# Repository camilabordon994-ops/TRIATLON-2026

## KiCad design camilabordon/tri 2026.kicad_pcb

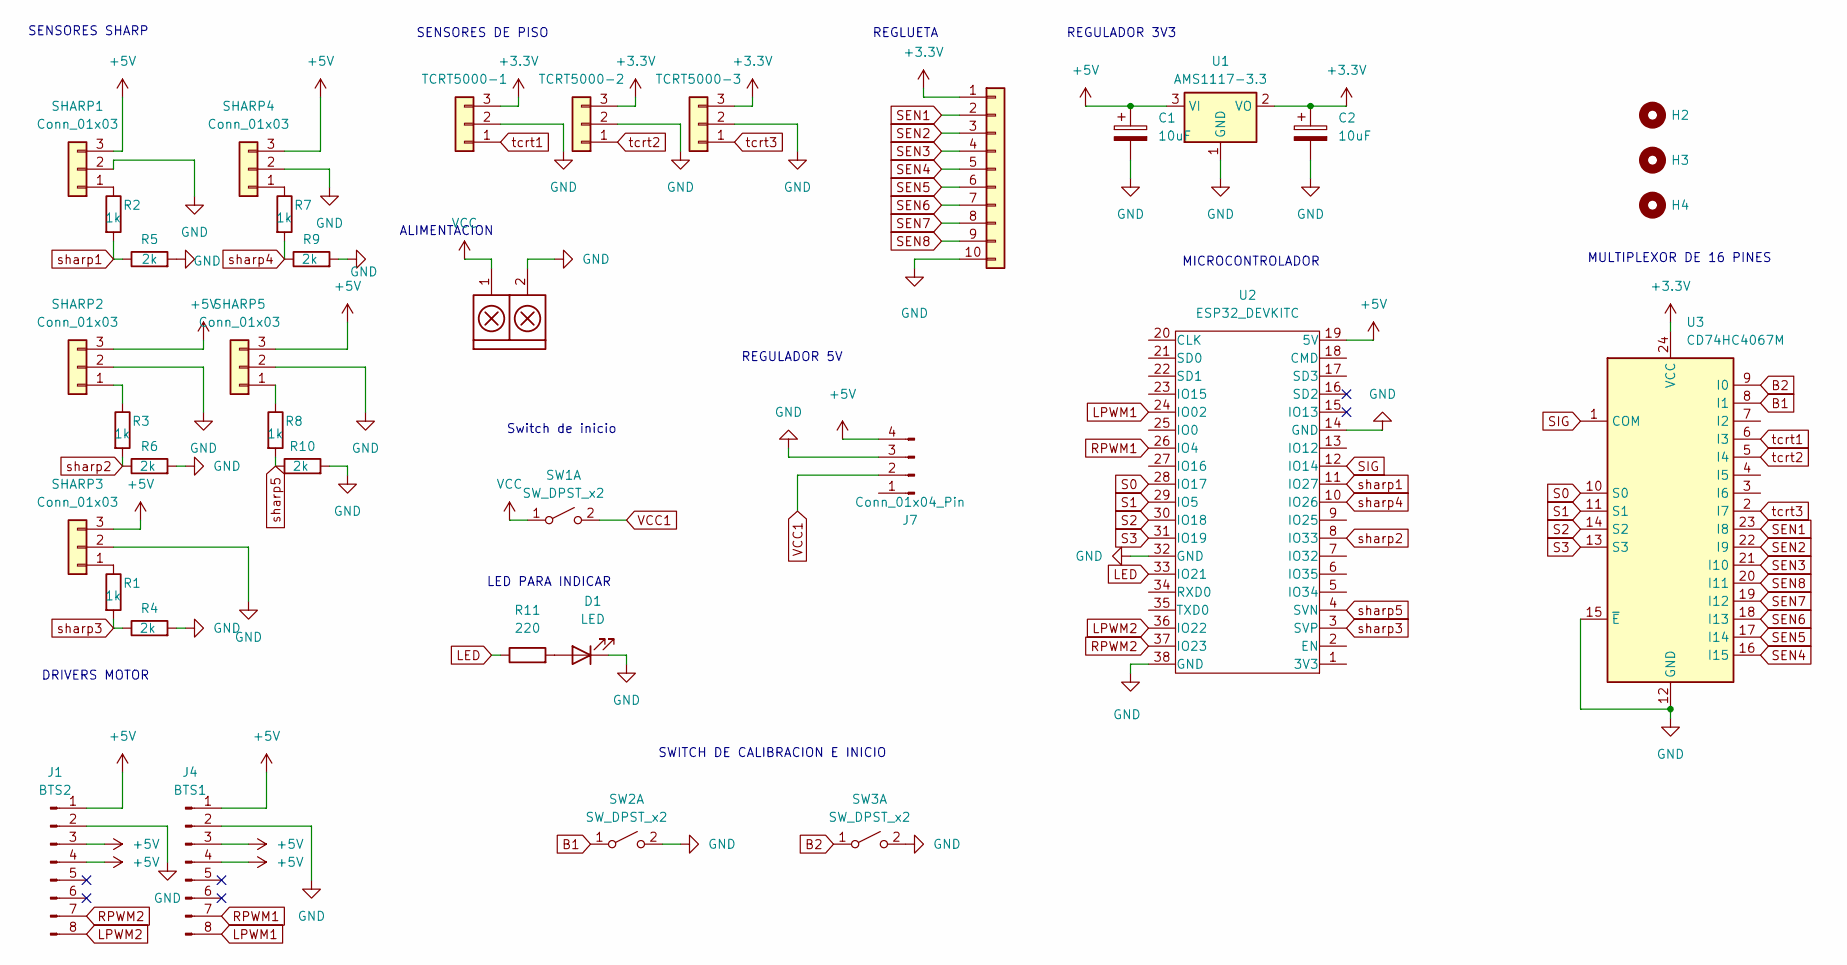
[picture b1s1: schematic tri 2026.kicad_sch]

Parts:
C1, C2: 10uF; C_0805_2012Metric
D1: LED; LED_D5.0mm
H2, H3, H4: Mounting_Hole; MountingHole_3.2mm_M3
J1: BTS2; IDC-Header_2x04_P2.54mm_Vertical
J2: TCRT5000-1; PinHeader_1x03_P2.54mm_Vertical
J3: TB_1X2; AMASS_XT30UPB-F_1x02_P5.0mm_Vertical
J4: BTS1; IDC-Header_2x04_P2.54mm_Vertical
J5: TCRT5000-2; PinHeader_1x03_P2.54mm_Vertical
J6: TCRT5000-3; PinHeader_1x03_P2.54mm_Vertical
J7: Conn_01x04_Pin; Step_Down_Mini
J8: Conn_01x10; JST_XH_S10B-XH-A_1x10_P2.50mm_Horizontal
R1, R2, R3, R7, R8: 1k; R_1206_3216Metric
R4, R5, R6, R9, R10: 2k; R_1206_3216Metric
R11: 220; R_1206_3216Metric
SHARP1, SHARP2, SHARP3, SHARP4, SHARP5: Conn_01x03; JST_XH_S3B-XH-A_1x03_P2.50mm_Horizontal
SW1: SW_DPST_x2; SW_SPDT_TH_Vertical
SW2, SW3: SW_DPST_x2; SW_PUSH_6mm_H5mm
U1: AMS1117-3.3; SOT-223-3_TabPin2
U2: ESP32_DEVKITC; esp32 38 pin usb-c
U3: CD74HC4067M; CD74HC4067_module

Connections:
+3.3V: C2.1, J2.3, J5.3, J6.3, J8.1, U1.2 (VO), U3.24 (VCC)
+5V: C1.1, J1.1, J1.3, J1.4, J4.1, J4.3, J4.4, J7.4, SHARP1.3, SHARP2.3, SHARP3.3, SHARP4.3, SHARP5.3, U1.3 (VI), U2.19 (5V)
B1: SW2.1 (A), U3.8 (I1)
B2: SW3.1 (A), U3.9 (I0)
GND: C1.2, C2.2, D1.1 (K), J1.2, J2.2, J3.2, J4.2, J5.2, J6.2, J7.3, J8.10, R4.2, R5.2, R6.2, R9.2, R10.2, SHARP1.2, SHARP2.2, SHARP3.2, SHARP4.2, SHARP5.2, SW2.2 (B), SW3.2 (B), U1.1 (GND), U2.14 (GND), U2.32 (GND), U2.38 (GND), U3.12 (GND), U3.15 (~E)
LED: R11.1, U2.33 (IO21)
LPWM1: J4.8, U2.24 (IO02)
LPWM2: J1.8, U2.36 (IO22)
unnamed: D1.2 (A), R11.2
unnamed: R2.1, SHARP1.1
unnamed: R3.1, SHARP2.1
unnamed: R1.1, SHARP3.1
unnamed: R7.1, SHARP4.1
unnamed: R8.1, SHARP5.1
RPWM1: J4.7, U2.26 (IO4)
RPWM2: J1.7, U2.37 (IO23)
S0: U2.28 (IO17), U3.10 (S0)
S1: U2.29 (IO5), U3.11 (S1)
S2: U2.30 (IO18), U3.14 (S2)
S3: U2.31 (IO19), U3.13 (S3)
SEN1: J8.2, U3.23 (I8)
SEN2: J8.3, U3.22 (I9)
SEN3: J8.4, U3.21 (I10)
SEN4: J8.5, U3.16 (I15)
SEN5: J8.6, U3.17 (I14)
SEN6: J8.7, U3.18 (I13)
SEN7: J8.8, U3.19 (I12)
SEN8: J8.9, U3.20 (I11)
SIG: U2.12 (IO14), U3.1 (COM)
VCC: J3.1, SW1.1 (A)
VCC1: J7.2, SW1.2 (B)
sharp1: R2.2, R5.1, U2.11 (IO27)
sharp2: R3.2, R6.1, U2.8 (IO33)
sharp3: R1.2, R4.1, U2.3 (SVP)
sharp4: R7.2, R9.1, U2.10 (IO26)
sharp5: R8.2, R10.1, U2.4 (SVN)
tcrt1: J2.1, U3.6 (I3)
tcrt2: J5.1, U3.5 (I4)
tcrt3: J6.1, U3.2 (I7)

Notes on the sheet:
Switch de inicio
ALIMENTACION
SENSORES DE PISO
LED PARA INDICAR
DRIVERS MOTOR
REGLUETA
MULTIPLEXOR DE 16 PINES
SWITCH DE CALIBRACION E INICIO
REGULADOR 3V3
REGULADOR 5V
SENSORES SHARP
MICROCONTROLADOR

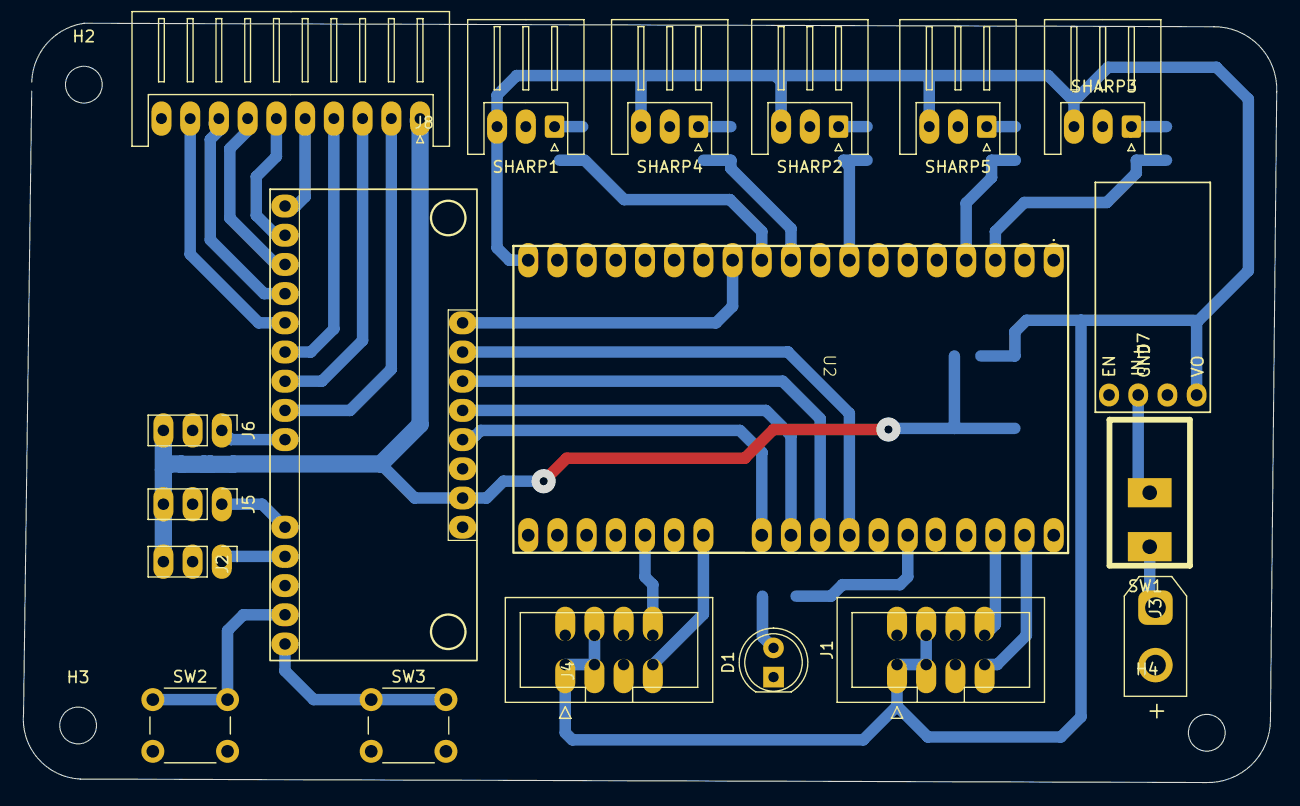
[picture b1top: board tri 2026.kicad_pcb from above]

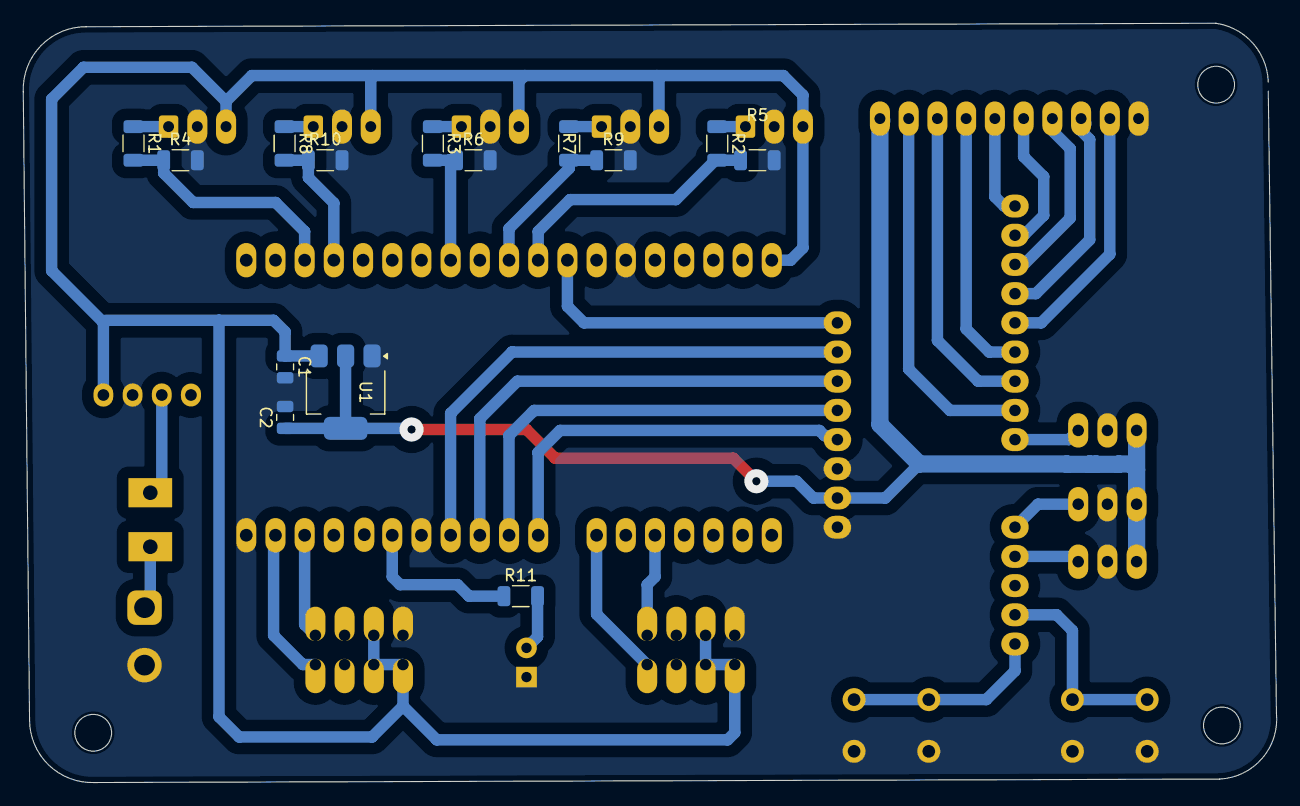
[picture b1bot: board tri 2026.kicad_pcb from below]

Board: 2 copper layers, 109.1 x 66.1 mm, 36 parts (14 on the bottom side), 39 nets.

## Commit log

2026-06-16 Rename tri 2026.kicad_pro to kicad/tri 2026.kicad_pro
2026-06-16 Rename CRS.kicad_mod to KICAD/CRS.kicad_mod
2026-06-16 Rename _autosave-tri 2026.kicad_prl to KICAD/_autosave-tri 2026.kicad_prl
2026-06-16 Rename _autosave-tri 2026.kicad_pro to KICAD/_autosave-tri 2026.kicad_pro
2026-06-16 Rename sym-lib-table to KICAD/sym-lib-table
2026-06-16 Rename fp-info-cache to KICAD/fp-info-cache
2026-06-16 Rename fp-lib-table to KICAD/fp-lib-table
2026-06-16 Rename tri 2026.kicad_pcb to KICAD/tri 2026.kicad_pcb
2026-06-16 Rename tri 2026.kicad_sch to KICAD/tri 2026.kicad_sch
2026-06-16 Rename tri 2026.kicad_prl to KICAD/tri 2026.kicad_prl
2026-06-16 Rename tri 2026.kicad_sch-bak to KICAD/tri 2026.kicad_sch-bak
